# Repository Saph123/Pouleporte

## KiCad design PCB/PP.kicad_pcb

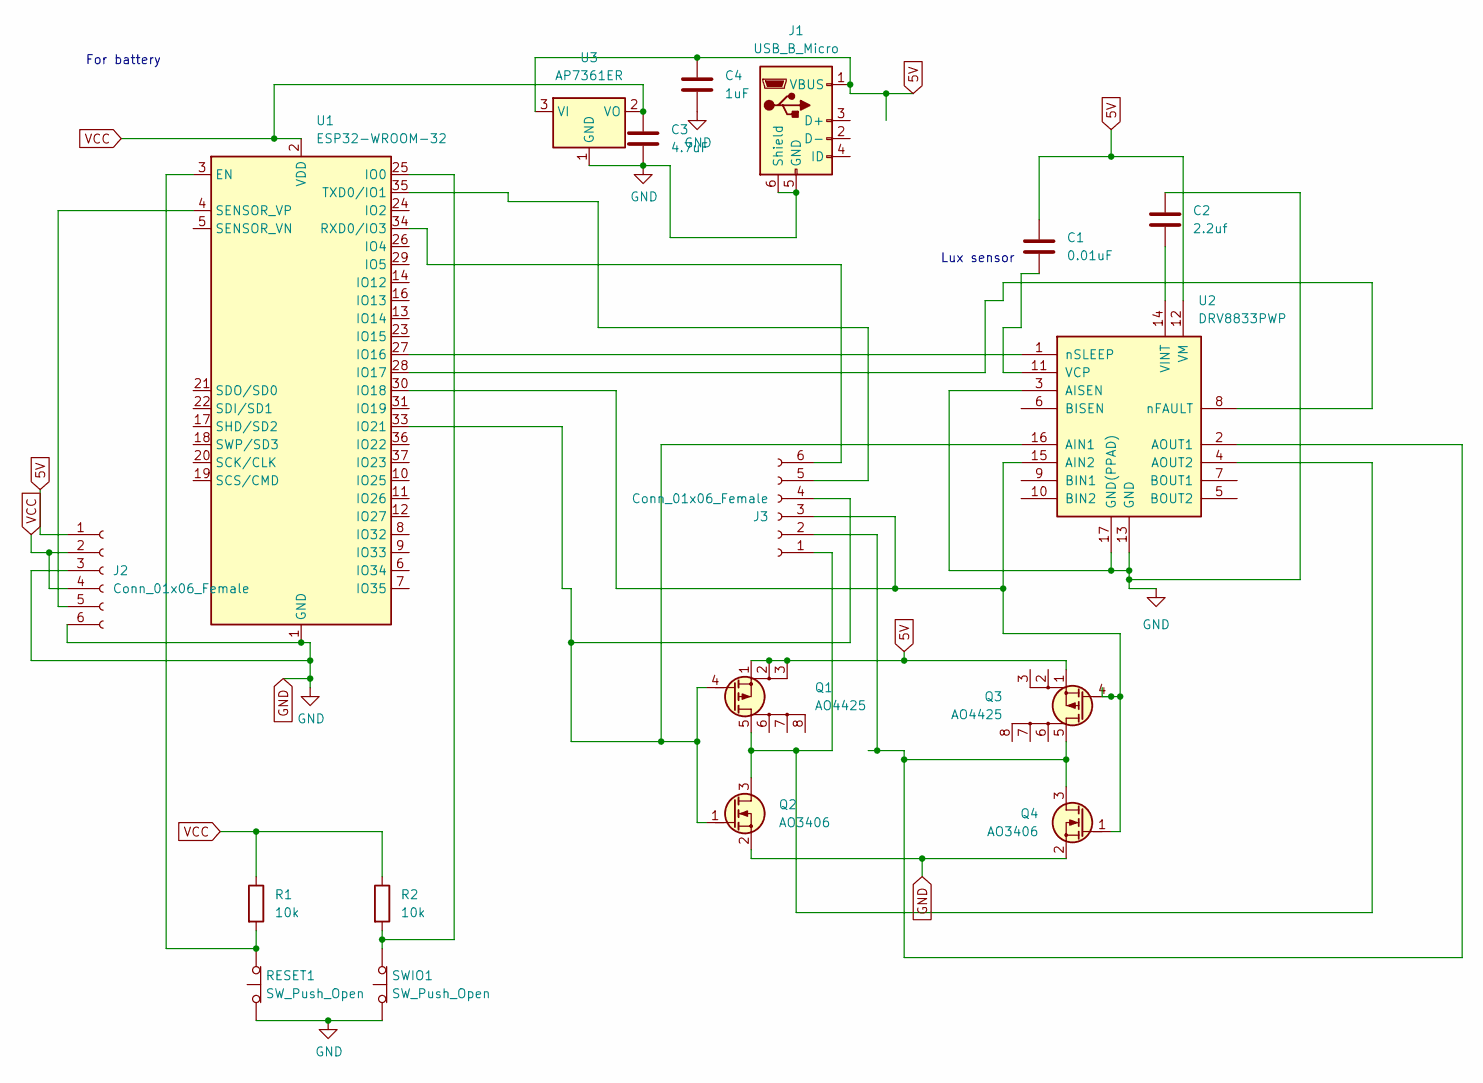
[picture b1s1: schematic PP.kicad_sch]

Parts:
C1: 0.01uF; C_0603_1608Metric
C2: 2.2uf; C_0603_1608Metric
C3: 4.7uF; C_0603_1608Metric
C4: 1uF; C_0603_1608Metric
J1: USB_B_Micro; USB_aliexpress
J2, J3: Conn_01x06_Female; TerminalBlock_Phoenix_MKDS-1,5-6_1x06_P5.00mm_Horizontal
Q1, Q3: AO4425; SO-8_3.9x4.9mm_P1.27mm
Q2, Q4: AO3406; SOT-23
R1, R2: 10k; C_0603_1608Metric
RESET1: SW_Push_Open; interrupteur
SWIO1: SW_Push_Open; interrupteur
U1: ESP32-WROOM-32
U2: DRV8833PWP; HTSSOP-16-1EP_4.4x5mm_P0.65mm_EP3.4x5mm_Mask2.46x2.31mm_The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
U3: AP7361ER; SOT-223-3_TabPin2

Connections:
5V: C1.1, C4.1, J1.1 (VBUS), J2.1, Q1.1 (S), Q1.2 (S), Q1.3 (S), Q3.1 (S), U2.12 (VM), U3.3 (VI)
GND: C2.1, C3.2, C4.2, J1.5 (GND), J1.6 (Shield), J2.3, J2.6, Q2.2 (S), Q4.2 (S), RESET1.1 (A), SWIO1.1 (A), U1.1 (GND), U1.15 (GND), U1.38 (GND), U1.39 (GND), U2.3 (AISEN), U2.13 (GND), U2.17 (GND(PPAD)), U3.1 (GND)
unnamed: C1.2, U2.11 (VCP)
unnamed: C2.2, U2.14 (VINT)
unnamed: J3.4, Q1.4 (G), Q2.1 (G), U1.33 (IO21), U2.16 (AIN1)
unnamed: J3.1, Q1.5 (D), Q2.3 (D), U2.4 (AOUT2)
unnamed: J3.3, Q3.4 (G), Q4.1 (G), U1.30 (IO18), U2.15 (AIN2)
unnamed: J3.2, Q3.5 (D), Q4.3 (D), U2.2 (AOUT1)
unnamed: R1.2, RESET1.2 (B), U1.3 (EN)
unnamed: R2.2, SWIO1.2 (B), U1.25 (IO0)
unnamed: J2.5, U1.4 (SENSOR_VP)
unnamed: U1.27 (IO16), U2.1 (nSLEEP)
unnamed: U1.28 (IO17), U2.8 (nFAULT)
unnamed: J3.6, U1.34 (RXD0/IO3)
unnamed: J3.5, U1.35 (TXD0/IO1)
VCC: C3.1, J2.2, J2.4, R1.1, R2.1, U1.2 (VDD), U3.2 (VO)

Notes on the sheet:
Lux sensor
For battery

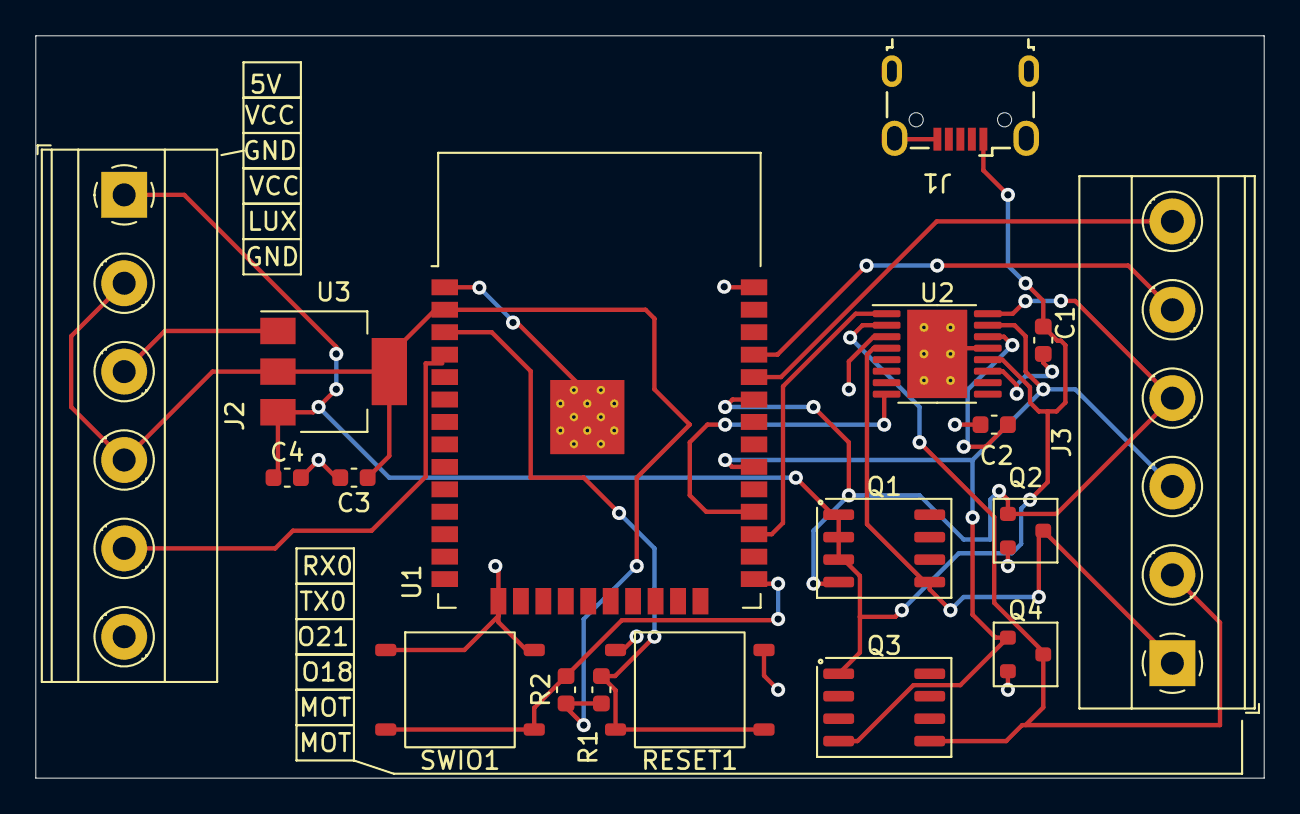
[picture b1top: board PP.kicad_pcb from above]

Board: 2 copper layers, 69.5 x 42.0 mm, 18 parts (0 on the bottom side), 16 nets.

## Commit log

2019-04-23 Original pouleporte code installed on 20/04
2019-04-23 Create ffff
2019-04-23 Removing ffff as it was useless
2019-04-23 Adding the first draft of PCB
2019-04-23 Added a footprint for devkit v1
2019-05-21 Clean of comments for wifi server that was not used anymore
2019-05-21 Adding a LED to GPIO 5
2019-05-21 Not tested: added val sensor1 when door closed
2019-05-21 Tested, seems to work Needs to be done: stop motor when door is detected!
2019-05-23 added motor.h and motor.cpp
2019-06-11 Door state toggle added
2019-06-11 change in print filter avant ouverture/fermeture phrase
2019-06-11 doorstatecmd in bluetooth
2019-06-11 added door state in print
2019-06-11 correction on println
2019-06-11 not finish yet but creating sensor hpp
2019-06-11 try to fix hpp
2019-06-11 not finished yet the motor.cpp yet need the door open status
2019-06-13 NVMEM OK
2019-06-13 VUU done safestate OK
2019-06-25 not done with the door status update auto
2019-06-26 new sensor to ADC2 ch2 pin D4/D2
2019-06-26 all correct I think... needs to be tested now
2019-06-26 ESP_BT print quand les etats de la porte sont chelou
2019-06-27 Passage en D34 sur l'ADC2
2019-06-27 update moteur
2019-06-27 avec les bons pinout du terrain!!
2019-07-01 code installed on 01/07/2019 sensors disabled
2019-07-09 new pcb! V1
2019-12-03 not fully tested, but BT deactivates after 5 mins
2019-12-08 delivery V2.0 08.12.19 with solar panel
2019-12-09 Ok without bluetooth cutoff!
2019-12-09 store firsttime in nvs store jour in nvs remove useless stuff with sensors
2021-10-22 adding moving average'
2022-04-24 Updated main cpp with 2 tempo, and fixed mean avg, installed on 24/04é
2022-12-05 Update pouleporte releaseV2
2022-12-08 adding all files in doubt
2022-12-21 adding usb and ap7361 libs
2022-12-21 Update schematic & pcb v3
2022-12-21 Gerber for V3
2023-01-22 not tested but full 9999 on STF/STO
2023-01-23 update with transistors mode
